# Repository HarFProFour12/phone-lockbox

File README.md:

# Tamagotchi Style Phone Lockbox

This is my custom phone lockbox that turns putting your phone away into a little game. All you have to do is put your phone inside, choose for how long you want to lock your phone, and let Byte (the tamagotchi character), keep you company while you stay off your phone.

## Features

* Phone locking for specific amount of time
* Tamagotchi character (Byte)
* Button-controlled UI
* 2" 240×320 SPI TFT IPS screen
* Adjustable lock time
* Adjustable screen brightness
* Battery indicator
* Locking mechanism controlled by solenoid lock

## Interface

The UI is designed with simple menus so it can be navigated using only four buttons (okay, back, up, down). The Home screen uses this layout:

* **Lock Phone**
* **Stats**
* **Settings**
* **About**

The Settings menu currently contains:

* **Lock Time**
* **Brightness**
* **Sounds**
* **System**

I've designed seperate sprites for Byte, including idle, happy, celebrating, excited, sad, thinking and sleeping, which change according to your actions.

## How It Works

The lockbox is controlled by an **ESP32-C6-DevKitC-1**. The display show the current screen and whether Byte's happy, sad, excited, etc.. You can control the UI using the 4 physical pushbuttons, which are left from the screen.

When you press "Lock Phone", the lock mechanism starts. First of all, the lipo battrey's current passed through a step=up converter and then activates the solenoid, which unlocks the box. From that time you have 5 seconds to put your phone inside. After that, the solenoid locks, locking yyour phone inside, and Byte's animation changes accordingly.

## Hardware

The current hardware includes the following components:

* ESP32
* Waveshare 2" 240×320 SPI TFT IPS IPS LCD
* 4× pushbuttons
* 12V solenoid lock
* 2000mAh 3.7V LiPo battery
* TP4056 Battery Charging module
* 2x DC-DC boost converter
* 1A 1000V 1N4007 Diode
* Mosfet IRLB8743P N-Channel 150A

## Schematic & Hardware Wiring

The lockbox uses an ESP32-C6 with two parallel step-up converters, which are powered by a 3.7V LiPo cell managed by a TP4056 charging module.

### Power Distribution
* LiPo Battery (3.7V): Connects to TP4056 B+ / B-.
* 3.7V Rail (TP4056 OUT+): Sends input to both boost converters and the voltage divider, which is used to be able to calculate the battery's percentage..
* MT3608 Boost (5V Output): Gives power the ESP32-C6 using the 5V0 pin.
* XL6009 Boost (12V Output): Supplies high voltage to the solenoid lock and also the 1N4007 flyback diode.
* Common Ground (OUT-): All module grounds, MOSFET source, and button rails are connected to the same GND.

## Project Structure

```text
Phone-Lockbox/
├── buttons.cpp
├── buttons.h
├── globals.cpp
├── globals.h
├── graphics.cpp
├── graphics.h
├── hardware.cpp
├── hardware.h
├── home.cpp
├── home.h
├── lock.cpp
├── lock.h
├── main.ino
├── settings.cpp
├── settings.h
├── stats.cpp
├── stats.h
├── ui.cpp
└── ui.h
```
I've split the many screens and functions into different files so it's easier to navigate and can be more easily debugged.

## Current Status

The project is still in the making process.

What I've done so far:

*  Basic TFT IPS interface
*  Home screen
*  Menu navigation
*  Settings screen
*  Lock time adjustment
*  Brightness adjustment
*  Byte animations
*  Solenoid control
*  Actual countdown timer
*  Complete Stats screen
*  Sounds
*  System settings
*  Battery monitoring
*  Complete lock/unlock logic
*  Final enclosure design

I have left to do:

* Getting the parts
* Final hardware assembly

## Design

The lockbox was designed around my **iPhone 13**, with the inside dimensions, and electronics compartment built around it. The box's inside measures to 91.5 mm × 166.7 mm. While phones with about the same dimensions to the iPhone 13 can also fit, it is not guaranteed.

The UI uses pixel-art inspired by tamagotchis.

Byte was designed by hand for this project using Piskel (an online tool), with different expressions that match what you do (e.g. put your phone away = happy, completed a session = celebrating, took it out too early = sad, etc.).

## Built With

* Arduino (C++)
* ESP32
* TFT_eSPI (Arduino Library)
* Fusion
* Piskel
* lopaka.app
* 3D printing

## AI Usage

I used AI, mainly for:

- Code debugging: fixing errors and debugging.
- Code structure: help split the code into separate files.
- Byte: generating an first prototype for how Byte would look, which I then recreated and edited myself in Piskel.

The actual project design, assembly, UI, gpraphics, and final code were done by me.

---
### Created for Hack Club’s Stardance.
This project was created as part of Hack Club Stardance, a Hack Club event encouraging young people to build and ship their own projects.

---
**Made by Harry Fanouriakis**

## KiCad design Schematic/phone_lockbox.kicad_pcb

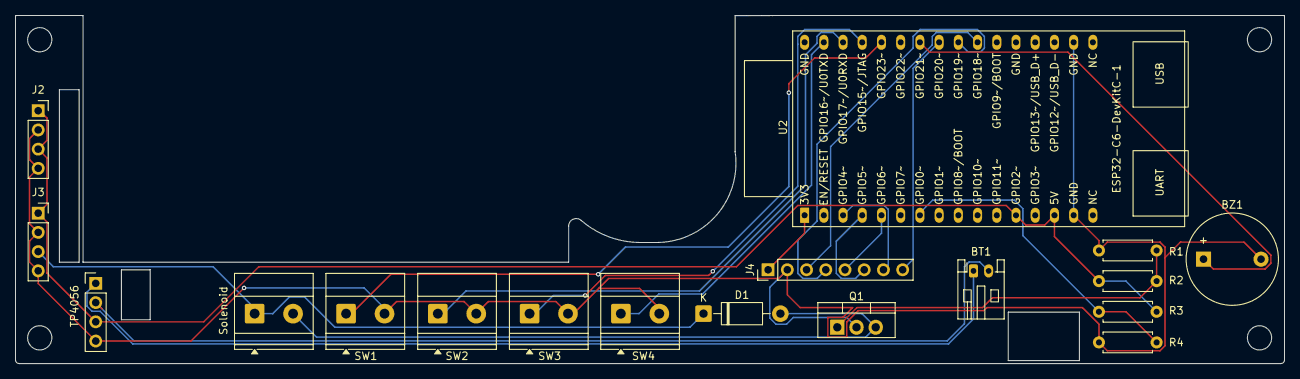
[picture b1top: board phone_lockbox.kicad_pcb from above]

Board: 2 copper layers, 167.7 x 46.0 mm, 18 parts (0 on the bottom side), 20 nets.

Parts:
BT1: Battery_Cell; JST_PH_S2B-PH-K_1x02_P2.00mm_Horizontal
BZ1: Buzzer; Buzzer_12x9.5RM7.6
D1: 1N4007; D_DO-41_SOD81_P10.16mm_Horizontal
J2: MT3608; PinSocket_1x04_P2.54mm_Vertical
J3: XL6009; PinSocket_1x04_P2.54mm_Vertical
J4: TFT_IPS_DISPLAY; PinHeader_1x08_P2.54mm_Vertical
Q1: Q_NMOS_GSD; TO-220-3_Vertical
R1, R3, R4: 10K; R_Axial_DIN0207_L6.3mm_D2.5mm_P7.62mm_Horizontal
R2: 220; R_Axial_DIN0207_L6.3mm_D2.5mm_P7.62mm_Horizontal
SW1: BACK; TerminalBlock_Phoenix_MKDS-1,5-2-5.08_1x02_P5.08mm_Horizont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
SW2: OK; TerminalBlock_Phoenix_MKDS-1,5-2-5.08_1x02_P5.08mm_Horizont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
SW3: UP; TerminalBlock_Phoenix_MKDS-1,5-2-5.08_1x02_P5.08mm_Horizont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
SW4: DOWN; TerminalBlock_Phoenix_MKDS-1,5-2-5.08_1x02_P5.08mm_Horizont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
Solenoid: 12V Solenoid; TerminalBlock_Phoenix_MKDS-1,5-2-5.08_1x02_P5.08mm_Horizont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
TP4056: TP4056; PinHeader_1x04_P2.54mm_Vertical
U2: ESP32-C6-DevKitC-1

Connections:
/+: D1.1 (K), J3.3, Solenoid.1
/-: D1.2 (A), Q1.3 (D), Solenoid.2
/B+: BT1.1 (+), TP4056.1
/B-: BT1.2 (-), TP4056.2
/BL: J4.8, U2.25 (GPIO20)
/CLK: J4.4, U2.24 (GPIO19)
/CS: J4.5, U2.5 (GPIO6)
/DC: J4.6, U2.4 (GPIO5/MTDI)
/DIN: J4.3, U2.23 (GPIO18)
/IN+: J2.1, J2.3, J3.1, R2.1, R3.2, TP4056.3, U2.12 (GPIO2), U2.14 (5V)
/RST: J4.7, U2.3 (GPIO4/MTMS)
/VCC: J4.1, U2.1 (3V3)
GND: BZ1.2 (-), J2.2, J2.4, J3.2, J3.4, J4.2, Q1.2 (S), R1.1, R4.1, SW1.2, SW2.2, SW3.2, SW4.2, TP4056.4, U2.15 (GND), U2.18 (GND)
unnamed: BZ1.1 (+), U2.26 (GPIO21)
unnamed: Q1.1 (G), R1.2, R2.2
unnamed: R3.1, R4.2, U2.7 (GPIO0)
unnamed: SW3.1, U2.29 (GPIO15/JTAG)
unnamed: SW4.1, U2.31 (GPIO16/U0TXD)
unnamed: SW2.1, U2.30 (GPIO17/U0RXD)
unnamed: SW1.1, U2.28 (GPIO23)
